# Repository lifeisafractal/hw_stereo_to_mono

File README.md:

# Simple Passive Stereo to Mono mixer

This is a really simple board that allows input of a stereo audio signal through a 3.5mm TRS jack and mixes together the left and right channels and outputs a dual mono signal on a 3.5mm TRS jack.

The design files were created using [KiCad](https://kicad-pcb.org/).

# Design
This works by using two resistors to mix the left and right signal. a decent impedance here will prevent major back driving of the source. The values need to also need to be small realitive to the input impedance of the device connected to the output. As the values get closer to each other, there will be excessive drop in volume. In general a value of 1k-3k should work for most cases.

There is also an extra pad for a divider on the mixer output that can be used to further lower the volume of the output. In general this should be left unpopulated.

A combination footprint was created allowing for either through hole or 0603 SMD resistors to be used.

# License
The hardware is released under [Creative Commons ShareAlike 4.0 International](https://creativecommons.org/licenses/by-sa/4.0/).

Distributed as-is; no warranty is given.

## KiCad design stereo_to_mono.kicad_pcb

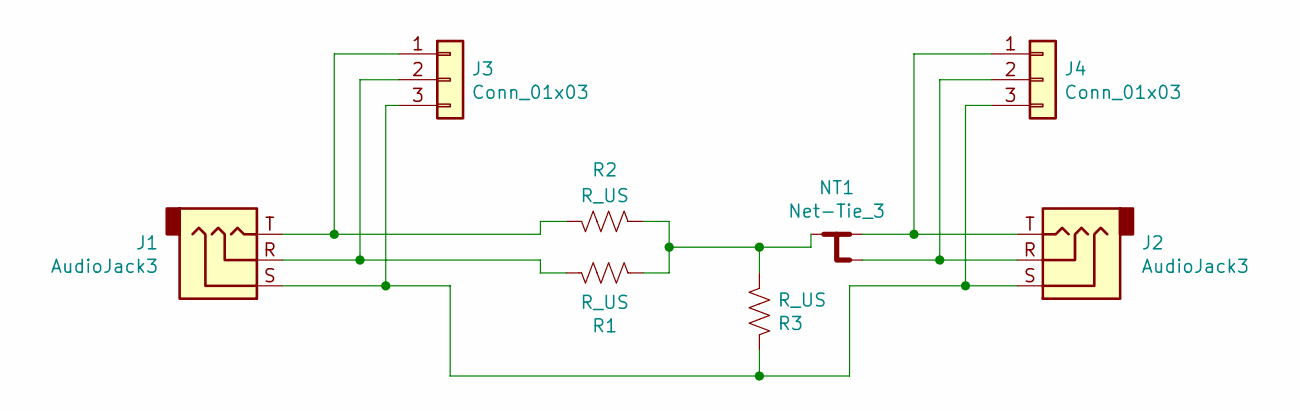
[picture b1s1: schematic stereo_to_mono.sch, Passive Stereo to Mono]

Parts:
J1, J2: AudioJack3; Jack_3.5mm_CUI_SJ1-3533NG_Horizontal; MPN SJ1-3533NG
J3, J4: Conn_01x03; PinHeader_1x03_P2.54mm_Vertical
NT1: Net-Tie_3; NetTie-3_SMD_Pad0.5mm
R1, R2, R3: R_US; R_Axial_DIN0207_L6.3mm_D2.5mm_P10.16mm_Horizontal

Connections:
unnamed: J1.R, J3.2, R1.2
unnamed: J1.S, J2.S, J3.3, J4.3, R3.2
unnamed: J1.T, J3.1, R2.2
unnamed: J2.R, J4.2, NT1.3
unnamed: J2.T, J4.1, NT1.1
unnamed: NT1.2, R1.1, R2.1, R3.1

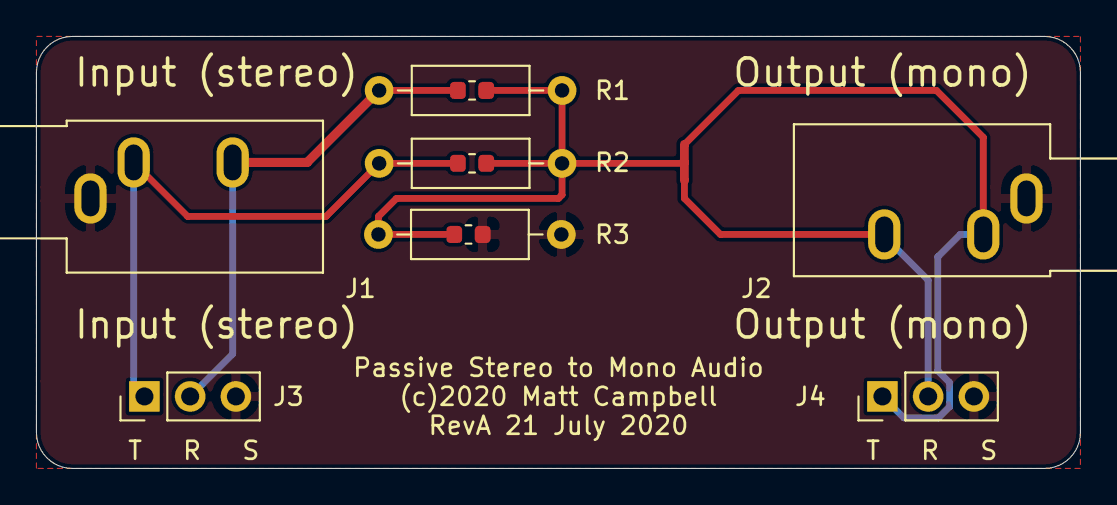
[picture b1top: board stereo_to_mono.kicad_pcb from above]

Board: 2 copper layers, 58.0 x 24.0 mm, 8 parts (0 on the bottom side), 6 nets.

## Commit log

2020-08-02 RevA
2020-08-02 remove the backup of the pcb
2020-08-02 Fix connects on teat headers
2020-08-02 Rename the fab package
2020-08-02 Add a picture

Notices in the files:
stereo_to_mono.kicad_pcb:
(c)2020 Matt Campbell
